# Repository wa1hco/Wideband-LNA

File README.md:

# Wideband-LNA
LNA with Qorvo TQP3M9036
~20 dB gain
~0.5 dB noise figure
50 MHz to 2 GHz
~8 dB return loss

Includes bias T option
Power from coax also available on USB-C

Input protection improved with inductor to ground.

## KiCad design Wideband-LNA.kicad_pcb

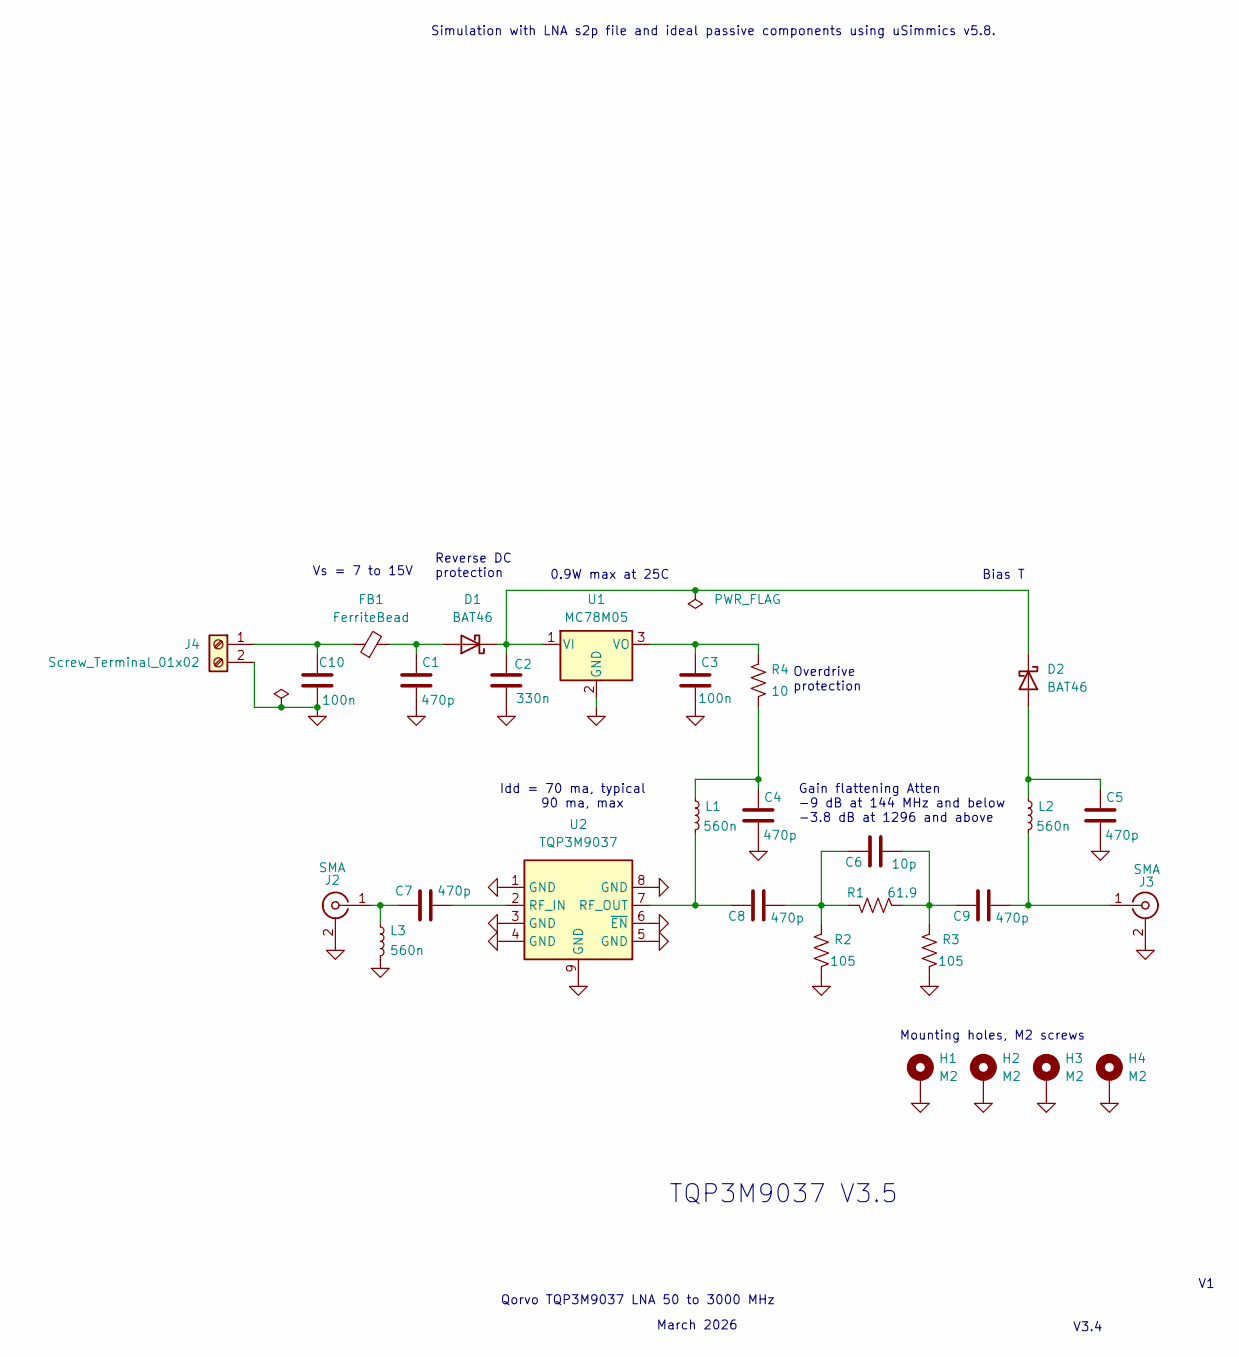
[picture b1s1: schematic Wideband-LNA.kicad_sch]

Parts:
C1, C4, C5, C7, C8, C9: 470p; C_0402_1005Metric; LCSC C20069335
C2: 330n; C_0402_1005Metric; LCSC C282682
C3: 100n; C_0402_1005Metric; LCSC C1525
C6: 10p; C_0603_1608Metric; LCSC C1634
C10: 100n; C_0402_1005Metric; LCSC C20069335
D1, D2: BAT46; D_SOD-523; LCSC C22466367
FB1: FerriteBead; L_0603_1608Metric; LCSC C1002
H1, H2, H3, H4: M2; MountingHole_3.5mm_Pad_Via
J2, J3: SMA; SMA_Amphenol_901-144_Vertical
J4: Screw_Terminal_01x02
L1, L2, L3: 560n; L_0603_1608Metric; LCSC C6808023
R1: 61.9; R_0603_1608Metric; LCSC C482904
R2, R3: 105; R_0603_1608Metric; LCSC C227541
R4: 10; R_0402_1005Metric; LCSC C25077
U1: MC78M05; TO-252-2; LCSC C94612
U2: TQP3M9037; DFN-8-1EP_2x2mm_P0.5mm_EP0.8x1.6mm; LCSC C415712

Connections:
GND: C1.2, C2.2, C3.2, C4.2, C5.2, C10.2, H1.1 (1_1), H2.1 (1_1), H3.1 (1_1), H4.1 (1_1), J2.2 (Ext), J3.2 (Ext), J4.2, L3.2, R2.2, R3.2, U1.2 (GND), U2.1 (GND), U2.3 (GND), U2.4 (GND), U2.5 (GND), U2.6 (~EN), U2.8 (GND), U2.9 (GND)
unnamed: C4.1, L1.1, R4.2
unnamed: C6.1, C8.2, R1.1, R2.1
unnamed: C6.2, C9.1, R1.2, R3.1
unnamed: C1.1, D1.2 (A), FB1.2
unnamed: C2.1, D1.1 (K), D2.1 (K), U1.1 (VI)
unnamed: C5.1, D2.2 (A), L2.1
unnamed: C7.1, J2.1 (In), L3.1
unnamed: C9.2, J3.1 (In), L2.2
unnamed: C10.1, FB1.1, J4.1
unnamed: C3.1, R4.1, U1.3 (VO)
unnamed: C7.2, U2.2 (RF_IN)
unnamed: C8.1, L1.2, U2.7 (RF_OUT)

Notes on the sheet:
TQP3M9037 V3.5
Bias T
Mounting holes, M2 screws
March 2026
Reverse DC protection
Gain flattening Atten -9 dB at 144 MHz and below -3.8 dB at 1296 and above
Overdrive protection
Simulation with LNA s2p file and ideal passive components using uSimmics v5.8.
0.9W max at 25C
V3.4
Vs = 7 to 15V
Qorvo TQP3M9037 LNA 50 to 3000 MHz
Idd = 70 ma, typical 90 ma, max

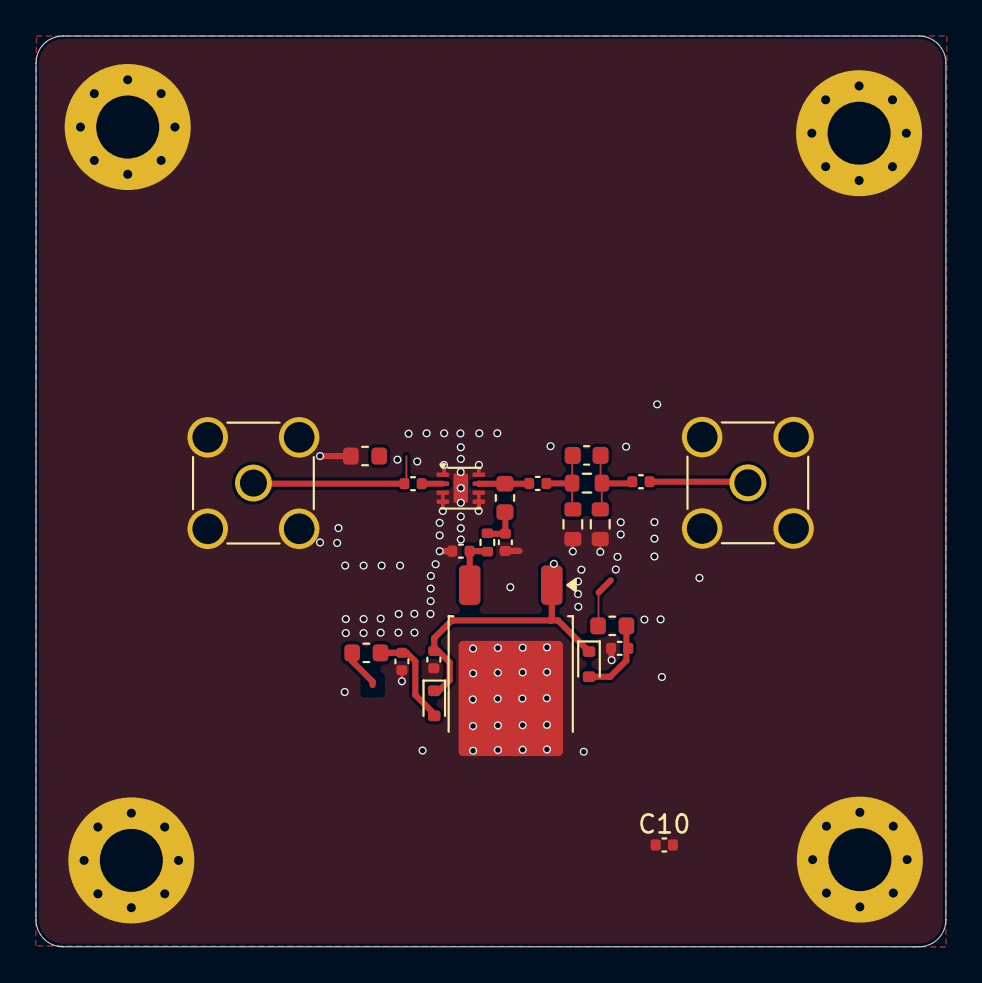
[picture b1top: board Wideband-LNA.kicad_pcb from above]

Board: 4 copper layers, 50.6 x 50.6 mm, 28 parts (0 on the bottom side), 13 nets.

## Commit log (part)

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2025-01-16 LNA with Qorvo TQP3M9037, 4 layer board with USB-C power connector.
2025-01-16 started moving libraries from single project to wa1hco global
2025-01-27 rename datasheets, tweak layout
2025-01-27 size to 24x24, tweaked layout
2025-01-27 changed to 50 to 2000 MHz, qorvo 9036, 68 nH choke
2025-01-29 M2 screw hole from via to mounting hole Increased radius of corners Reduced side to 18.8 mm to allow clearance in enclosure Increase size of notch for SMA pin Added into to back silkscreen
2025-01-31 added SO323 diodes to input for protection. Added experiment for power over coax. Added id and copyright to back silkscreen. changed screw vias to mounting holes reduced size to 18.8 x 18.8 mm for to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
2025-02-01 Added power over output coax, forwarding to USB-C Changed input protection from OVP diodes to Inductor to ground.
2025-02-13 Added input L to ground and L on output for bias T. Diode to prevent USB-C power from flowing back down coax But allow power from coax to exit from USB-C to power relays, etc.
2025-02-18 Fix input inductor connection.
2025-02-25 added pdfs for board and schematic
2025-03-16 updated design to match input at 144 MHz based on uSimmics modeling added 10 ohm resistor in power lead per suggestion from ZMS
2025-06-05 New variant with MiniCircuits PGA-103
2025-09-25 Added 2 dB pad to the output Rearranged components to fit more tightly Recalculated trace width of 0.35 when working against 2nd layer Added inner layer keepouts under pads in 50 Ohm path for better 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
2025-09-25 Review layout
2025-09-27 Improve stability with circuit from App Note Improve low frequency coverage Added uSimmics files Added bias T to enable powering from coax Made inductors smaller so everything fits
2025-11-12 After the fab and assy, components error fixes
2025-11-14 Relayout for 25x25x50 extruded aluminum enclosure Axial coax connectors Isolation of LNA input and output Extensive shielding vias around RF traces
2025-11-18 Branch for 2nd spin of V3 - move DC traces to layer 3 - leave layer 2 ground under component pads
2025-11-19 Removed cut outs under RF component pads Add stitching vias around all RF components Ensured two vias tied to ground planes for each RF component ground pads Improved layout to return ground currents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
2025-11-21 Change from PGA103+ to TQP3M9036 for the 50x25x25 enclosure
2025-11-22 Update layout to 19x19 enclosure, TQP3M9036 Improved ground via to isolate voltage regulator circuit from input goal of improving stability Add solder mask relief near output to improve contact with 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
2025-11-22 Revised description on back skilkscreen
2025-12-02 Updated sheet titles to show Version and Git Branch
2025-12-02 Added pdf of schematic and layout drawings
2025-12-03 Added footprint for minicircuits TCCH-80+ output choke
2025-12-10 added dimensions for enclosure end caps
    Add jlcpcb impedance calculator results
2025-12-10 Add zone mask to relieve ground plane under component pads
    Added screen shot of JLCPCB impedance calculator
    Removed bias T components
2025-12-14 Preparing for fab and assy
2025-12-16 Added s2p models, simulated with attenuator and flattened gain simulated 9036 and 9037 updated schematic and layout to remove bias T and LED, prep for attenuator
2025-12-18 Added attenuator with high frequency bypass on output
2025-12-19 Added uSimmics folder and simulations for TQP3M9036 and 9037
2025-12-22 Updated jlcpcb components
2025-12-23 Changed inductors for input antistatic and DC choke
2025-12-26 added bias T changed from USB-C to feed through
2025-12-30 Optimize layout for 0603 components Change from USB-C to pad for feedthrough capacitor Change regulator to 78L05
2026-01-02 Relayout for 8-32 feedthrough capacitor Relayout for larger DPAK voltage regulator, allows high input voltage Had to remove 10 Ohm series resistor in LNA supply lead Reduced size of ferrite bead to 0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
2026-01-02 Remove stray ground layer mask
2026-01-04 Selected components for manufacturing, generated JLCPCB files
2026-01-07 Released for production at jlcpcb on Jan 5, 2026 Double checked the jlcpcb tool component selection from LCSC stock
2026-05-16 Stop tracking JLCPCB generated files
2026-05-16 catching up, first commit of test code that uses the noise figure meter
2026-05-16 Add LNA bench test harness under test/lna_bench
2026-05-17 lna_bench: add mock mode and preflight CLI commands
2026-05-18 lna_bench: port bench settings, add probe_scpi.py, add pytest suite
    - station.example.toml: 10 MHz-3 GHz/401 pts sweep, ham band key
    frequencies (50/144/222/432/903/1296/2304 MHz), 300 s VISA timeout,
    FETC:CORR:NFIG?/GAIN? commands, empty prepare list, INIT:CONT ON
    apply + verify check
    - probe_scpi.py: standalone VISA REPL for bench troubleshooting
    - tests/test_config.py: 8 tests covering all ported settings
2026-05-18 lna_bench: add streamlit GUI and compact report updates
2026-05-18 hardware: remove obsolete design docs and update schematic

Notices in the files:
Wideband-LNA.kicad_pcb:
Creative Commons License V4
